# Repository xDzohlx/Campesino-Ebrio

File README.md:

# Campesino-Ebrio Robot de combate de 12 lb. 

Este es el robot mas completo que he desarrollado.

Ha competido en 4 competencias y actualmente es la versión 3 del robot.

Talent land 2019
Primer competencia del campesino
Tryta 2019
Al no recibir mucho daño tecnicamente se volvio a construir y volvio a competir
Motorama robot conflict 2020
Subcampeon del torneo y primer evento internacional donde se compitió
Norwalk Havoc Robot League 6 feb 2021
Tercer lugar de 4 robots inscritos no se tuvo muy buen desempeño
Norwalk Havoc Robot League Junio 2021
Norwalk Havoc Robot League Finalist Diciembre 2021
Motorama Robot Conflict 2022
Norwalk Havoc Robot League Octubre 2023

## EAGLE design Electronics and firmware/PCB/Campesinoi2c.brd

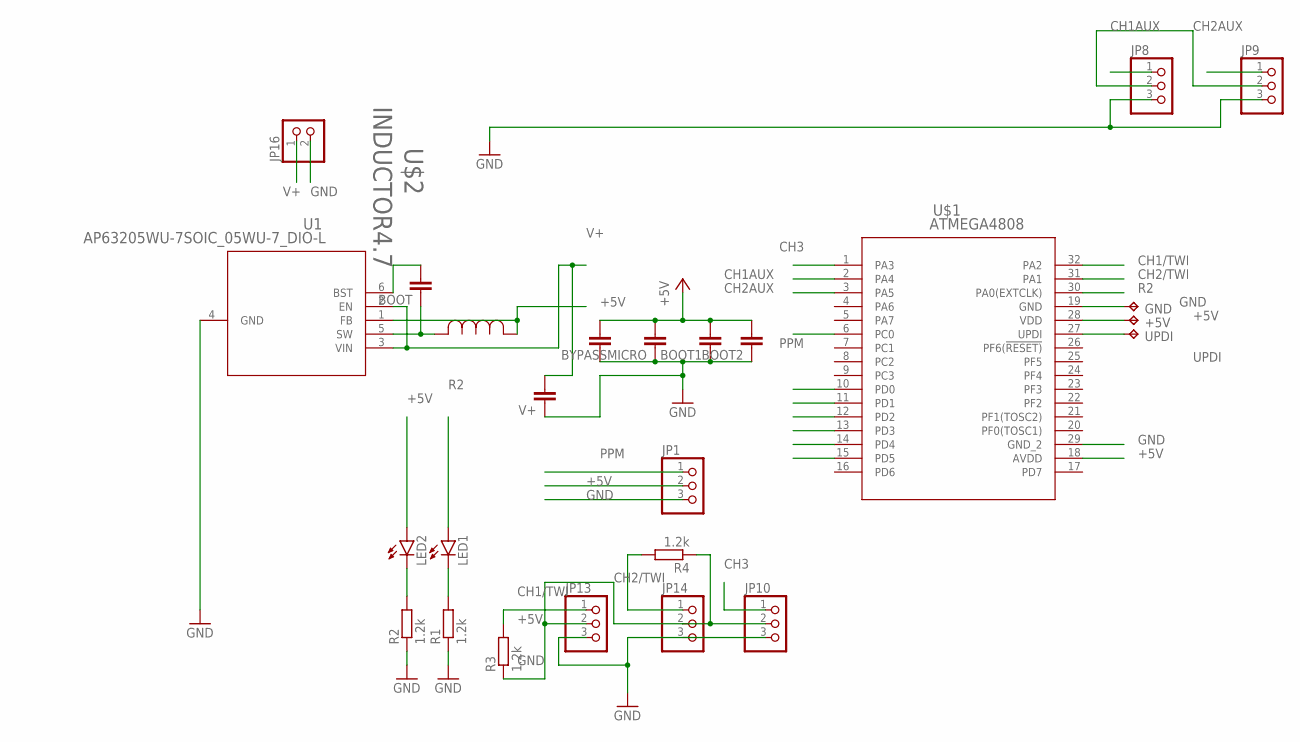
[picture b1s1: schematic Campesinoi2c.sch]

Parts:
+5V: TPB1,27; B1,27
BOOT, BOOT1, BOOT2: C-EUC0402; C0402
BYPASSMICRO, BYPASSMICRO2: C-EUC0603; C0603
GND: TPB1,27; B1,27
JP1, JP8, JP9, JP10, JP13, JP14: PINHD-1X03_2.54-S; 1X03-S
JP16: PINHD-1X02_2.54-S; 1X02-S
LED1, LED2: LEDCHIPLED_0603; CHIPLED_0603
R1, R2, R3, R4: 1.2k; R0603
U1: AP63205WU-7SOIC_05WU-7_DIO-L; SOIC_05WU-7_DIO-L
U$1: ATMEGA4808; QFP80P900X900X120-32N
U$2: INDUCTOR4.7; IND_NRS5030T100MMGJ_TAY
UPDI: TPB1,27; B1,27
V+: C-EUC1206; C1206

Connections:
+5V: +5V.TP, BOOT1.2, BOOT2.2, BYPASSMICRO.2, BYPASSMICRO2.2, JP1.2, JP8.2, JP9.2, JP10.2, JP13.2, JP14.2, LED2.A, R3.1, R4.1, U1.1 (FB), U$1.18 (AVDD), U$1.28 (VDD), U$2.1
CH1/TWI: JP13.1, R3.2, U$1.32 (PA2)
CH1AUX: JP8.1, U$1.2 (PA4)
CH2/TWI: JP14.1, R4.2, U$1.31 (PA1)
CH2AUX: JP9.1, U$1.3 (PA5)
CH3: JP10.1, U$1.1 (PA3)
GND: BOOT1.1, BOOT2.1, BYPASSMICRO.1, BYPASSMICRO2.1, GND.TP, JP1.3, JP8.3, JP9.3, JP10.3, JP13.3, JP14.3, JP16.2, R1.1, R2.1, U1.4 (GND), U$1.19 (GND), U$1.29 (GND_2), V+.1
unnamed: LED2.C, R2.2
unnamed: LED1.C, R1.2
unnamed: BOOT.1, U1.5 (SW), U$2.2
unnamed: BOOT.2, U1.6 (BST)
PPM: JP1.1, U$1.6 (PC0)
R2: LED1.A, U$1.30 (PA0(EXTCLK))
SENSOR1: U$1.10 (PD0)
SENSOR2: U$1.11 (PD1)
SENSOR3: U$1.12 (PD2)
SENSOR4: U$1.13 (PD3)
SENSOR5: U$1.14 (PD4)
SENSOR6: U$1.15 (PD5)
UPDI: U$1.27 (UPDI), UPDI.TP
V+: JP16.1, U1.2 (EN), U1.3 (VIN), V+.2

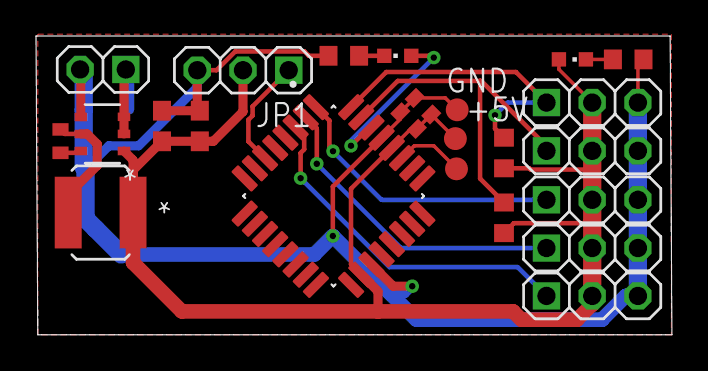
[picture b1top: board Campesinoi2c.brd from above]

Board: 2 copper layers, 35.3 x 16.6 mm, 25 parts (1 on the bottom side), 15 nets.

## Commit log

2021-03-10 Add files via upload
    Diseño en solidworks de mi robot el campesino ebrio
2021-04-05 Create Electronics and firmware
2021-04-05 Create Firmware
2021-04-05 Create Lista de material
2021-04-05 Rename Firmware to Test
2021-04-05 Create DecodificadorPPM.c
    Decodificador para receptor de PPM sin PWM. Estsa probado en Norwalk en 6 de febrero de 2021
2021-04-07 Create Cad
2021-04-09 Create PCBS
2021-07-11 Create Comportamiento central.c
    Programa de prueba para sistema autónomo, lectura de señales de entrada y sensores
2021-07-12 Update Comportamiento central.c
    Ya estan todos los modulos actualizados y funcionales
2021-07-16 Se agregaron los controladores
    Se agregaron los controladores, las validaciones y los seguros.
2021-08-06 Update Comportamiento central.c
    Update sensor to read less sensors, working on mixer for upside down driving
2021-08-06 test
2021-08-06 Working version with flip switch
2021-08-09 Update reversa y tiempo
    Trabajo en progreso para reversa automática con un filtro y un vector de tiempo en ms, la parte del vector ya funciona a 32 bits pero el switch automatico tiene problemas
2021-08-14 Prueba
    Prueba exitosa del sistema de conducción asistida los sensores si centran un objeto pero necesitan ser filtrados. Se leen dos sensores y al parecer se necesita un controlador D solo tiene controlador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
2021-08-14 Nuevas piezas mejoradas
2021-09-02 Version probada en nueva placa
    Version funcionando los motores con rtc y sensores adc falta generador de trayectorias y planeador de trayectorias
2021-09-03 Tested and updated
2021-09-04 Seleccion de modo con RC
    Funciona bien la selección pero no funciona al momento de mandar las señales o paro
2021-09-05 Adelante en maximo funciona
2021-09-05 Funciona el vector para ir adelante
2021-09-05 Funcionan giros
2021-09-09 Ya gira a la izquierda
2021-09-09 update generador de trayectorias
    Generador de trayectorias actualizado, tiene una funcion para girar a ala izquida y otra a la derecha , ya esta funcionando y esta probado en el robot fura del debug
2021-09-09 Solo le falta dar bien una vuelta
2021-09-24 Update Comportamiento central.c
    Sensor de reversa funcional
2021-09-28 Acelerometro mejorado
    Se agrego la característica de sumador del ADC para un promediador del filtro por hardware agregando la asistencia en la conducción pero no esta probado
2021-09-28 Acelerometro probado
2021-09-28 Vref actualizado
    Acelerometro probado
2021-09-29 Controlador de tracción funcionando
    Controlador de tracción funcionando y sin oscilaciones. Controla aceleración y giro con muy buen desempeño elimina casi totalmente el sobrebirage y es mucho mas facil ir derecho
2021-12-02 Create Comportamientocentral
2021-12-02 Create Comportamiento central
2022-02-24 Add files via upload
    last version working in NHRL finals and Motorama 2022
2023-07-29 Update to Sbus
    Sbus funcionando a 2 canales falta agregar funcionalidad a la cinematica inversa
2023-08-06 Add files via upload
    este funciona
2023-08-14 Update main.c
    PWM emulado para arma,
2023-09-29 Update main.c
    last minute change
2023-12-05 Delete Cad directory
    New version to be uploaded
2023-12-05 Create New.txt
    New folder
2023-12-05 Update del cad
2024-09-04 Funciona adelante, reversa y selector
2024-10-22 Body control con lanzallamas y servo
2025-09-22 Add stl files for structure and weapon

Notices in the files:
parts and their libraries:
COPYRIGHT: Copyright (C) 2018 Accelerated Designs. All rights reserved
